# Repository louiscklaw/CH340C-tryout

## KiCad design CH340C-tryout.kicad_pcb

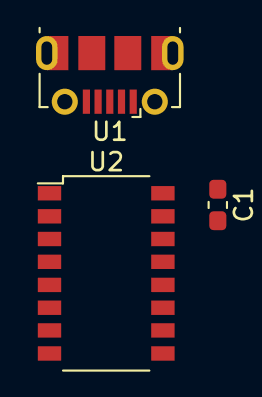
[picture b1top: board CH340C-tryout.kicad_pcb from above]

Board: 2 copper layers, 3 parts (0 on the bottom side), 4 nets, no tracks yet.

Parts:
C1: C104,0603; C_0603_1608Metric_Pad1.05x0.95mm_HandSolder
U1: USB_Micro; USB_Micro-B_Molex-105017-0001
U2: CH340C

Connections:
+3V3: C1.2, U2.4, U2.16
GND: C1.1, U1.5, U1.6, U1.7, U1.8, U1.9, U2.1
unnamed: U1.2, U2.6
unnamed: U1.3, U2.5

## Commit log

2019-06-14 update,.
2020-05-05 ci: init travis token,
2020-05-05 ci: init travis build config,
